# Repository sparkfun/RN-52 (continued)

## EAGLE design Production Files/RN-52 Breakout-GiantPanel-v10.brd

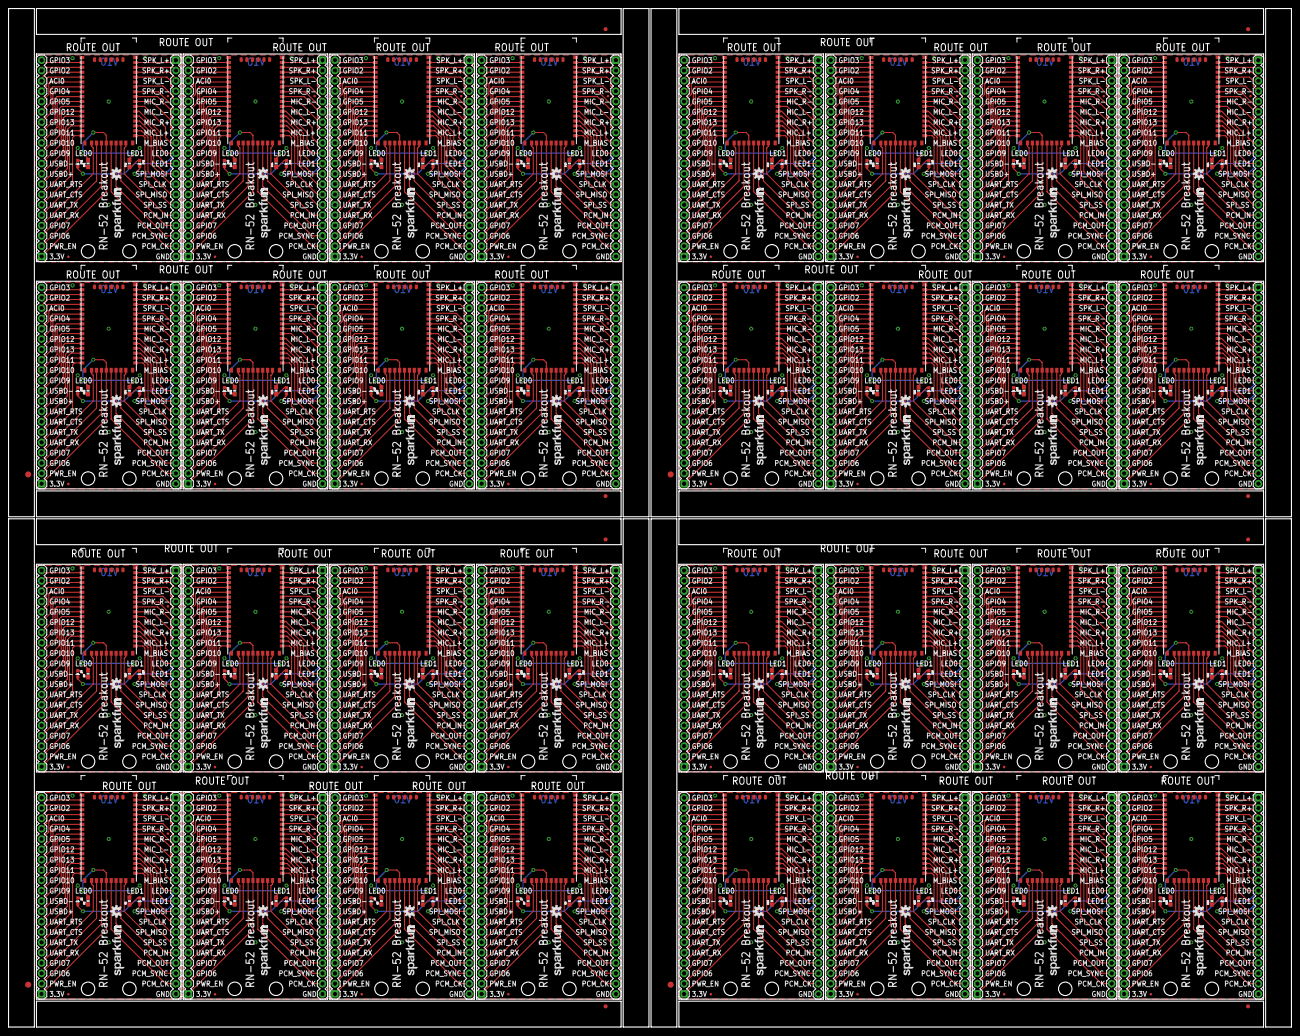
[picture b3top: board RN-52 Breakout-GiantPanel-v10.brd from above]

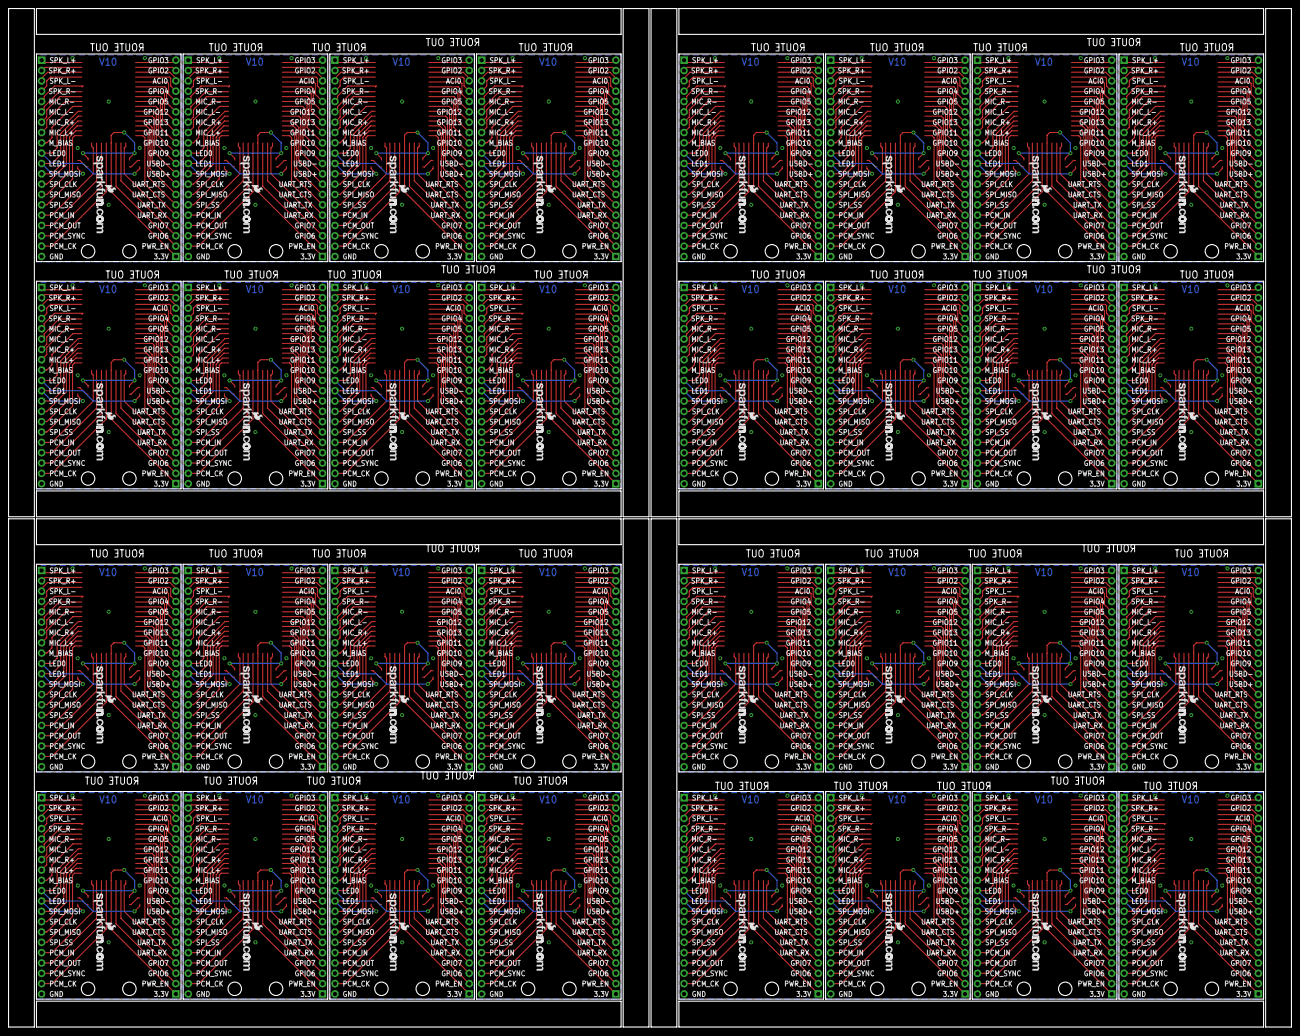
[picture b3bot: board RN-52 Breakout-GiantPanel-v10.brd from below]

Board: 2 copper layers, 315.5 x 250.4 mm, 460 parts (32 on the bottom side), 1344 nets.

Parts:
D1, D3, D5, D7, D9, D11, D13, D15, D17, D19, D21, D23, D25, D27, D29, D31, D33, D35, D37, D39, D41, D43, D45, D47, D49, D51, D53, D55, D57, D59, D61, D63: GREEN; LED-0603
D2, D4, D6, D8, D10, D12, D14, D16, D18, D20, D22, D24, D26, D28, D30, D32, D34, D36, D38, D40, D42, D44, D46, D48, D50, D52, D54, D56, D58, D60, D62, D64: RED; LED-0603
E$1, E$2, E$3, E$4, E$5, E$6, E$7, E$8, E$9, E$10, E$11, E$12, E$13, E$14, E$15, E$16, E$18, E$20, E$21, E$22, E$23, E$25, E$26, E$27, E$28, E$29, E$30, E$31, E$32, E$33, E$34, E$35, E$39, E$40, E$41, E$42, E$43, E$44, E$45, E$46, E$47, E$48, E$49, E$50, E$51, E$52, E$53, E$54, E$58, E$59, E$60, E$61, E$62, E$63, E$64, E$65, E$66, E$67, E$68, E$69, E$70, E$71, E$72, E$73: MICRO-FIDUCIAL
E$17, E$38, E$57, E$76: FIDUCIAL-1.5X3
E$19, E$24, E$36, E$37, E$55, E$56, E$74, E$75: FIDUCIAL-1X2
JP1, JP2, JP3, JP4, JP5, JP6, JP7, JP8, JP9, JP10, JP11, JP12, JP13, JP14, JP15, JP16, JP17, JP18, JP19, JP20, JP21, JP22, JP23, JP24, JP25, JP26, JP27, JP28, JP29, JP30, JP31, JP32, JP33, JP34, JP35, JP36, JP37, JP38, JP39, JP40, JP41, JP42, JP43, JP44, JP45, JP46, JP47, JP48, JP49, JP50, JP51, JP52, JP53, JP54, JP55, JP56, JP57, JP58, JP59, JP60, JP61, JP62, JP63, JP64: M20; 1X20
LOGO1, LOGO2, LOGO7, LOGO10, LOGO13, LOGO16, LOGO19, LOGO22, LOGO25, LOGO28, LOGO31, LOGO34, LOGO37, LOGO40, LOGO43, LOGO46, LOGO49, LOGO52, LOGO55, LOGO58, LOGO61, LOGO64, LOGO67, LOGO70, LOGO73, LOGO76, LOGO79, LOGO82, LOGO85, LOGO88, LOGO91, LOGO94: OSHW-LOGOS; OSHW-LOGO-S
LOGO3, LOGO5, LOGO8, LOGO11, LOGO14, LOGO17, LOGO20, LOGO23, LOGO26, LOGO29, LOGO32, LOGO35, LOGO38, LOGO41, LOGO44, LOGO47, LOGO50, LOGO53, LOGO56, LOGO59, LOGO62, LOGO65, LOGO68, LOGO71, LOGO74, LOGO77, LOGO80, LOGO83, LOGO86, LOGO89, LOGO92, LOGO95: LOGO-SFENEW; SFE-NEW-WEBLOGO
LOGO4, LOGO6, LOGO9, LOGO12, LOGO15, LOGO18, LOGO21, LOGO24, LOGO27, LOGO30, LOGO33, LOGO36, LOGO39, LOGO42, LOGO45, LOGO48, LOGO51, LOGO54, LOGO57, LOGO60, LOGO63, LOGO66, LOGO69, LOGO72, LOGO75, LOGO78, LOGO81, LOGO84, LOGO87, LOGO90, LOGO93, LOGO96: LOGO-SFENW2; SFE-NEW-WEB
R1, R2, R3, R4, R5, R6, R7, R8, R9, R10, R11, R12, R13, R14, R15, R16, R17, R18, R19, R20, R21, R22, R23, R24, R25, R26, R27, R28, R29, R30, R31, R32, R33, R34, R35, R36, R37, R38, R39, R40, R41, R42, R43, R44, R45, R46, R47, R48, R49, R50, R51, R52, R53, R54, R55, R56, R57, R58, R59, R60, R61, R62, R63, R64: 330; 0603-RES
STANDOFF1, STANDOFF2, STANDOFF3, STANDOFF4, STANDOFF5, STANDOFF6, STANDOFF7, STANDOFF8, STANDOFF9, STANDOFF10, STANDOFF11, STANDOFF12, STANDOFF13, STANDOFF14, STANDOFF15, STANDOFF16, STANDOFF17, STANDOFF18, STANDOFF19, STANDOFF20, STANDOFF21, STANDOFF22, STANDOFF23, STANDOFF24, STANDOFF25, STANDOFF26, STANDOFF27, STANDOFF28, STANDOFF29, STANDOFF30, STANDOFF31, STANDOFF32, STANDOFF33, STANDOFF34, STANDOFF35, STANDOFF36, STANDOFF37, STANDOFF38, STANDOFF39, STANDOFF40, STANDOFF41, STANDOFF42, STANDOFF43, STANDOFF44, STANDOFF45, STANDOFF46, STANDOFF47, STANDOFF48, STANDOFF49, STANDOFF50, STANDOFF51, STANDOFF52, STANDOFF53, STANDOFF54, STANDOFF55, STANDOFF56, STANDOFF57, STANDOFF58, STANDOFF59, STANDOFF60, STANDOFF61, STANDOFF62, STANDOFF63, STANDOFF64: STAND-OFF
U1, U2, U3, U4, U5, U6, U7, U8, U9, U10, U11, U12, U13, U14, U15, U16, U17, U18, U19, U20, U21, U22, U23, U24, U25, U26, U27, U28, U29, U30, U31, U32: BLUETOOTH-RN-52; RN-52

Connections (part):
3.3V: JP1.1, R1.2, R2.2, U1.20
3.3V1: JP3.1, R3.2, R4.2, U2.20
3.3V2: JP5.1, R5.2, R6.2, U3.20
3.3V3: JP7.1, R7.2, R8.2, U4.20
3.3V4: JP9.1, R9.2, R10.2, U5.20
3.3V5: JP11.1, R11.2, R12.2, U6.20
3.3V6: JP13.1, R13.2, R14.2, U7.20
3.3V7: JP15.1, R15.2, R16.2, U8.20
3.3V8: JP17.1, R17.2, R18.2, U9.20
3.3V9: JP19.1, R19.2, R20.2, U10.20
3.3V10: JP21.1, R21.2, R22.2, U11.20
3.3V11: JP23.1, R23.2, R24.2, U12.20
3.3V12: JP25.1, R25.2, R26.2, U13.20
3.3V13: JP27.1, R27.2, R28.2, U14.20
3.3V14: JP29.1, R29.2, R30.2, U15.20
3.3V15: JP31.1, R31.2, R32.2, U16.20
3.3V16: JP33.1, R33.2, R34.2, U17.20
3.3V17: JP35.1, R35.2, R36.2, U18.20
3.3V18: JP37.1, R37.2, R38.2, U19.20
3.3V19: JP39.1, R39.2, R40.2, U20.20
3.3V20: JP41.1, R41.2, R42.2, U21.20
3.3V21: JP43.1, R43.2, R44.2, U22.20
3.3V22: JP45.1, R45.2, R46.2, U23.20
3.3V23: JP47.1, R47.2, R48.2, U24.20
3.3V24: JP49.1, R49.2, R50.2, U25.20
3.3V25: JP51.1, R51.2, R52.2, U26.20
3.3V26: JP53.1, R53.2, R54.2, U27.20
3.3V27: JP55.1, R55.2, R56.2, U28.20
3.3V28: JP57.1, R57.2, R58.2, U29.20
3.3V29: JP59.1, R59.2, R60.2, U30.20
3.3V30: JP61.1, R61.2, R62.2, U31.20
3.3V31: JP63.1, R63.2, R64.2, U32.20
AIC0: JP1.18, U1.3
AIC1: JP3.18, U2.3
AIC2: JP5.18, U3.3
AIC3: JP7.18, U4.3
AIC4: JP9.18, U5.3
AIC5: JP11.18, U6.3
AIC6: JP13.18, U7.3
AIC7: JP15.18, U8.3
AIC8: JP17.18, U9.3
AIC9: JP19.18, U10.3
AIC10: JP21.18, U11.3
AIC11: JP23.18, U12.3
AIC12: JP25.18, U13.3
AIC13: JP27.18, U14.3
AIC14: JP29.18, U15.3
AIC15: JP31.18, U16.3
AIC16: JP33.18, U17.3
AIC17: JP35.18, U18.3
AIC18: JP37.18, U19.3
AIC19: JP39.18, U20.3
AIC20: JP41.18, U21.3
AIC21: JP43.18, U22.3
AIC22: JP45.18, U23.3
AIC23: JP47.18, U24.3
AIC24: JP49.18, U25.3
AIC25: JP51.18, U26.3
AIC26: JP53.18, U27.3
AIC27: JP55.18, U28.3
AIC28: JP57.18, U29.3
AIC29: JP59.18, U30.3
AIC30: JP61.18, U31.3
AIC31: JP63.18, U32.3
GND: JP2.20, U1.36, U1.G1, U1.G2, U1.G3, U1.G4, U1.RFG1, U1.RFG2, U1.RFG3, U1.RFG4, U1.RFG5, U1.RFG6
GND1: JP4.20, U2.36, U2.G1, U2.G2, U2.G3, U2.G4, U2.RFG1, U2.RFG2, U2.RFG3, U2.RFG4, U2.RFG5, U2.RFG6
GND2: JP6.20, U3.36, U3.G1, U3.G2, U3.G3, U3.G4, U3.RFG1, U3.RFG2, U3.RFG3, U3.RFG4, U3.RFG5, U3.RFG6
GND3: JP8.20, U4.36, U4.G1, U4.G2, U4.G3, U4.G4, U4.RFG1, U4.RFG2, U4.RFG3, U4.RFG4, U4.RFG5, U4.RFG6
GND4: JP10.20, U5.36, U5.G1, U5.G2, U5.G3, U5.G4, U5.RFG1, U5.RFG2, U5.RFG3, U5.RFG4, U5.RFG5, U5.RFG6
GND5: JP12.20, U6.36, U6.G1, U6.G2, U6.G3, U6.G4, U6.RFG1, U6.RFG2, U6.RFG3, U6.RFG4, U6.RFG5, U6.RFG6
GND6: JP14.20, U7.36, U7.G1, U7.G2, U7.G3, U7.G4, U7.RFG1, U7.RFG2, U7.RFG3, U7.RFG4, U7.RFG5, U7.RFG6
GND7: JP16.20, U8.36, U8.G1, U8.G2, U8.G3, U8.G4, U8.RFG1, U8.RFG2, U8.RFG3, U8.RFG4, U8.RFG5, U8.RFG6
GND8: JP18.20, U9.36, U9.G1, U9.G2, U9.G3, U9.G4, U9.RFG1, U9.RFG2, U9.RFG3, U9.RFG4, U9.RFG5, U9.RFG6
GND9: JP20.20, U10.36, U10.G1, U10.G2, U10.G3, U10.G4, U10.RFG1, U10.RFG2, U10.RFG3, U10.RFG4, U10.RFG5, U10.RFG6
GND10: JP22.20, U11.36, U11.G1, U11.G2, U11.G3, U11.G4, U11.RFG1, U11.RFG2, U11.RFG3, U11.RFG4, U11.RFG5, U11.RFG6
GND11: JP24.20, U12.36, U12.G1, U12.G2, U12.G3, U12.G4, U12.RFG1, U12.RFG2, U12.RFG3, U12.RFG4, U12.RFG5, U12.RFG6
GND12: JP26.20, U13.36, U13.G1, U13.G2, U13.G3, U13.G4, U13.RFG1, U13.RFG2, U13.RFG3, U13.RFG4, U13.RFG5, U13.RFG6
GND13: JP28.20, U14.36, U14.G1, U14.G2, U14.G3, U14.G4, U14.RFG1, U14.RFG2, U14.RFG3, U14.RFG4, U14.RFG5, U14.RFG6
GND14: JP30.20, U15.36, U15.G1, U15.G2, U15.G3, U15.G4, U15.RFG1, U15.RFG2, U15.RFG3, U15.RFG4, U15.RFG5, U15.RFG6
GND15: JP32.20, U16.36, U16.G1, U16.G2, U16.G3, U16.G4, U16.RFG1, U16.RFG2, U16.RFG3, U16.RFG4, U16.RFG5, U16.RFG6
GND16: JP34.20, U17.36, U17.G1, U17.G2, U17.G3, U17.G4, U17.RFG1, U17.RFG2, U17.RFG3, U17.RFG4, U17.RFG5, U17.RFG6
GND17: JP36.20, U18.36, U18.G1, U18.G2, U18.G3, U18.G4, U18.RFG1, U18.RFG2, U18.RFG3, U18.RFG4, U18.RFG5, U18.RFG6
GND18: JP38.20, U19.36, U19.G1, U19.G2, U19.G3, U19.G4, U19.RFG1, U19.RFG2, U19.RFG3, U19.RFG4, U19.RFG5, U19.RFG6
GND19: JP40.20, U20.36, U20.G1, U20.G2, U20.G3, U20.G4, U20.RFG1, U20.RFG2, U20.RFG3, U20.RFG4, U20.RFG5, U20.RFG6
GND20: JP42.20, U21.36, U21.G1, U21.G2, U21.G3, U21.G4, U21.RFG1, U21.RFG2, U21.RFG3, U21.RFG4, U21.RFG5, U21.RFG6
GND21: JP44.20, U22.36, U22.G1, U22.G2, U22.G3, U22.G4, U22.RFG1, U22.RFG2, U22.RFG3, U22.RFG4, U22.RFG5, U22.RFG6
GND22: JP46.20, U23.36, U23.G1, U23.G2, U23.G3, U23.G4, U23.RFG1, U23.RFG2, U23.RFG3, U23.RFG4, U23.RFG5, U23.RFG6
GND23: JP48.20, U24.36, U24.G1, U24.G2, U24.G3, U24.G4, U24.RFG1, U24.RFG2, U24.RFG3, U24.RFG4, U24.RFG5, U24.RFG6
GND24: JP50.20, U25.36, U25.G1, U25.G2, U25.G3, U25.G4, U25.RFG1, U25.RFG2, U25.RFG3, U25.RFG4, U25.RFG5, U25.RFG6
GND25: JP52.20, U26.36, U26.G1, U26.G2, U26.G3, U26.G4, U26.RFG1, U26.RFG2, U26.RFG3, U26.RFG4, U26.RFG5, U26.RFG6
GND26: JP54.20, U27.36, U27.G1, U27.G2, U27.G3, U27.G4, U27.RFG1, U27.RFG2, U27.RFG3, U27.RFG4, U27.RFG5, U27.RFG6
GND27: JP56.20, U28.36, U28.G1, U28.G2, U28.G3, U28.G4, U28.RFG1, U28.RFG2, U28.RFG3, U28.RFG4, U28.RFG5, U28.RFG6
GND28: JP58.20, U29.36, U29.G1, U29.G2, U29.G3, U29.G4, U29.RFG1, U29.RFG2, U29.RFG3, U29.RFG4, U29.RFG5, U29.RFG6
GND29: JP60.20, U30.36, U30.G1, U30.G2, U30.G3, U30.G4, U30.RFG1, U30.RFG2, U30.RFG3, U30.RFG4, U30.RFG5, U30.RFG6
GND30: JP62.20, U31.36, U31.G1, U31.G2, U31.G3, U31.G4, U31.RFG1, U31.RFG2, U31.RFG3, U31.RFG4, U31.RFG5, U31.RFG6
GND31: JP64.20, U32.36, U32.G1, U32.G2, U32.G3, U32.G4, U32.RFG1, U32.RFG2, U32.RFG3, U32.RFG4, U32.RFG5, U32.RFG6
GPIO1: JP3.20, U2.1
GPIO2: JP1.19, U1.2
GPIO3: JP1.20, U1.1
GPIO4: JP1.17, U1.4
GPIO5: JP1.16, U1.5
GPIO6: JP1.3, U1.18
GPIO7: JP1.4, U1.17
GPIO8: JP3.19, U2.2
GPIO9: JP1.11, U1.10
GPIO10: JP1.12, U1.9
GPIO11: JP1.13, U1.8
GPIO12: JP1.15, U1.6
GPIO13: JP1.14, U1.7
GPIO14: JP3.17, U2.4
GPIO15: JP3.16, U2.5
GPIO16: JP3.15, U2.6
GPIO17: JP3.14, U2.7
GPIO18: JP3.13, U2.8
GPIO19: JP3.12, U2.9
GPIO20: JP3.11, U2.10
GPIO21: JP3.4, U2.17
GPIO22: JP3.3, U2.18
GPIO23: JP5.20, U3.1
GPIO24: JP5.19, U3.2
GPIO25: JP5.17, U3.4
GPIO26: JP5.16, U3.5
GPIO27: JP5.15, U3.6
GPIO28: JP5.14, U3.7
GPIO29: JP5.13, U3.8
GPIO30: JP5.12, U3.9
GPIO31: JP5.11, U3.10
GPIO32: JP5.4, U3.17
GPIO33: JP5.3, U3.18
GPIO34: JP7.20, U4.1
GPIO35: JP7.19, U4.2
GPIO36: JP7.17, U4.4
GPIO37: JP7.16, U4.5
GPIO38: JP7.15, U4.6
GPIO39: JP7.14, U4.7
GPIO40: JP7.13, U4.8
GPIO41: JP7.12, U4.9
GPIO42: JP7.11, U4.10
GPIO43: JP7.4, U4.17
GPIO44: JP7.3, U4.18
GPIO45: JP9.20, U5.1
GPIO46: JP9.19, U5.2
GPIO47: JP9.17, U5.4
GPIO48: JP9.16, U5.5
GPIO49: JP9.15, U5.6
GPIO50: JP9.14, U5.7
GPIO51: JP9.13, U5.8
GPIO52: JP9.12, U5.9
GPIO53: JP9.11, U5.10
GPIO54: JP9.4, U5.17
GPIO55: JP9.3, U5.18
GPIO56: JP11.20, U6.1
GPIO57: JP11.19, U6.2
GPIO58: JP11.17, U6.4
GPIO59: JP11.16, U6.5
GPIO60: JP11.15, U6.6
GPIO61: JP11.14, U6.7
GPIO62: JP11.13, U6.8
GPIO63: JP11.12, U6.9
GPIO64: JP11.11, U6.10
GPIO65: JP11.4, U6.17
GPIO66: JP11.3, U6.18
GPIO67: JP13.20, U7.1
GPIO68: JP13.19, U7.2
GPIO69: JP13.17, U7.4
GPIO70: JP13.16, U7.5
GPIO71: JP13.15, U7.6
GPIO72: JP13.14, U7.7
GPIO73: JP13.13, U7.8
GPIO74: JP13.12, U7.9
GPIO75: JP13.11, U7.10
GPIO76: JP13.4, U7.17
GPIO77: JP13.3, U7.18
GPIO78: JP15.20, U8.1
GPIO79: JP15.19, U8.2
GPIO80: JP15.17, U8.4
GPIO81: JP15.16, U8.5
GPIO82: JP15.15, U8.6
GPIO83: JP15.14, U8.7
GPIO84: JP15.13, U8.8
GPIO85: JP15.12, U8.9
GPIO86: JP15.11, U8.10
GPIO87: JP15.4, U8.17
GPIO88: JP15.3, U8.18
GPIO89: JP17.20, U9.1
GPIO90: JP17.19, U9.2
GPIO91: JP17.17, U9.4
GPIO92: JP17.16, U9.5
GPIO93: JP17.15, U9.6
GPIO94: JP17.14, U9.7
GPIO95: JP17.13, U9.8
GPIO96: JP17.12, U9.9
GPIO97: JP17.11, U9.10
GPIO98: JP17.4, U9.17
GPIO99: JP17.3, U9.18
GPIO100: JP19.20, U10.1
GPIO101: JP19.19, U10.2
GPIO102: JP19.17, U10.4
GPIO103: JP19.16, U10.5
GPIO104: JP19.15, U10.6
GPIO105: JP19.14, U10.7
GPIO106: JP19.13, U10.8
GPIO107: JP19.12, U10.9
GPIO108: JP19.11, U10.10
GPIO109: JP19.4, U10.17
GPIO110: JP19.3, U10.18
GPIO111: JP21.20, U11.1
GPIO112: JP21.19, U11.2
GPIO113: JP21.17, U11.4
GPIO114: JP21.16, U11.5
GPIO115: JP21.15, U11.6
GPIO116: JP21.14, U11.7
GPIO117: JP21.13, U11.8
GPIO118: JP21.12, U11.9
GPIO119: JP21.11, U11.10
GPIO120: JP21.4, U11.17
GPIO121: JP21.3, U11.18
GPIO122: JP23.20, U12.1
GPIO123: JP23.19, U12.2
GPIO124: JP23.17, U12.4
GPIO125: JP23.16, U12.5
GPIO126: JP23.15, U12.6
GPIO127: JP23.14, U12.7
GPIO128: JP23.13, U12.8
GPIO129: JP23.12, U12.9
GPIO130: JP23.11, U12.10
GPIO131: JP23.4, U12.17
GPIO132: JP23.3, U12.18
GPIO133: JP25.20, U13.1
GPIO134: JP25.19, U13.2
GPIO135: JP25.17, U13.4
GPIO136: JP25.16, U13.5
GPIO137: JP25.15, U13.6
GPIO138: JP25.14, U13.7
GPIO139: JP25.13, U13.8
GPIO140: JP25.12, U13.9
GPIO141: JP25.11, U13.10
GPIO142: JP25.4, U13.17
GPIO143: JP25.3, U13.18
GPIO144: JP27.20, U14.1
GPIO145: JP27.19, U14.2
GPIO146: JP27.17, U14.4
GPIO147: JP27.16, U14.5
GPIO148: JP27.15, U14.6
GPIO149: JP27.14, U14.7
GPIO150: JP27.13, U14.8
GPIO151: JP27.12, U14.9
GPIO152: JP27.11, U14.10
GPIO153: JP27.4, U14.17
GPIO154: JP27.3, U14.18
GPIO155: JP29.20, U15.1
GPIO156: JP29.19, U15.2
GPIO157: JP29.17, U15.4
GPIO158: JP29.16, U15.5
GPIO159: JP29.15, U15.6
GPIO160: JP29.14, U15.7
GPIO161: JP29.13, U15.8
GPIO162: JP29.12, U15.9
GPIO163: JP29.11, U15.10
GPIO164: JP29.4, U15.17
GPIO165: JP29.3, U15.18
GPIO166: JP31.20, U16.1
GPIO167: JP31.19, U16.2
GPIO168: JP31.17, U16.4
GPIO169: JP31.16, U16.5
GPIO170: JP31.15, U16.6
GPIO171: JP31.14, U16.7
GPIO172: JP31.13, U16.8
GPIO173: JP31.12, U16.9
GPIO174: JP31.11, U16.10
GPIO175: JP31.4, U16.17
GPIO176: JP31.3, U16.18
GPIO177: JP33.20, U17.1
GPIO178: JP33.19, U17.2
GPIO179: JP33.17, U17.4
GPIO180: JP33.16, U17.5
GPIO181: JP33.15, U17.6
GPIO182: JP33.14, U17.7
GPIO183: JP33.13, U17.8
GPIO184: JP33.12, U17.9
GPIO185: JP33.11, U17.10
GPIO186: JP33.4, U17.17
GPIO187: JP33.3, U17.18
GPIO188: JP35.20, U18.1
GPIO189: JP35.19, U18.2
GPIO190: JP35.17, U18.4
GPIO191: JP35.16, U18.5
GPIO192: JP35.15, U18.6
GPIO193: JP35.14, U18.7
GPIO194: JP35.13, U18.8
GPIO195: JP35.12, U18.9
GPIO196: JP35.11, U18.10
GPIO197: JP35.4, U18.17
GPIO198: JP35.3, U18.18
GPIO199: JP37.20, U19.1
GPIO200: JP37.19, U19.2
GPIO201: JP37.17, U19.4
GPIO202: JP37.16, U19.5
GPIO203: JP37.15, U19.6
GPIO204: JP37.14, U19.7
GPIO205: JP37.13, U19.8
GPIO206: JP37.12, U19.9
GPIO207: JP37.11, U19.10
GPIO208: JP37.4, U19.17
GPIO209: JP37.3, U19.18
GPIO210: JP39.20, U20.1
GPIO211: JP39.19, U20.2
GPIO212: JP39.17, U20.4
GPIO213: JP39.16, U20.5
GPIO214: JP39.15, U20.6
GPIO215: JP39.14, U20.7
GPIO216: JP39.13, U20.8
GPIO217: JP39.12, U20.9
GPIO218: JP39.11, U20.10
GPIO219: JP39.4, U20.17
GPIO220: JP39.3, U20.18
GPIO221: JP41.20, U21.1
GPIO222: JP41.19, U21.2
GPIO223: JP41.17, U21.4
GPIO224: JP41.16, U21.5
GPIO225: JP41.15, U21.6
GPIO226: JP41.14, U21.7
GPIO227: JP41.13, U21.8
GPIO228: JP41.12, U21.9
GPIO229: JP41.11, U21.10
GPIO230: JP41.4, U21.17
GPIO231: JP41.3, U21.18
GPIO232: JP43.20, U22.1
GPIO233: JP43.19, U22.2
GPIO234: JP43.17, U22.4
GPIO235: JP43.16, U22.5
GPIO236: JP43.15, U22.6
GPIO237: JP43.14, U22.7
GPIO238: JP43.13, U22.8
GPIO239: JP43.12, U22.9
GPIO240: JP43.11, U22.10
GPIO241: JP43.4, U22.17
GPIO242: JP43.3, U22.18
GPIO243: JP45.20, U23.1
GPIO244: JP45.19, U23.2
GPIO245: JP45.17, U23.4
GPIO246: JP45.16, U23.5
GPIO247: JP45.15, U23.6
GPIO248: JP45.14, U23.7
GPIO249: JP45.13, U23.8
GPIO250: JP45.12, U23.9
GPIO251: JP45.11, U23.10
GPIO252: JP45.4, U23.17
GPIO253: JP45.3, U23.18
GPIO254: JP47.20, U24.1
GPIO255: JP47.19, U24.2
GPIO256: JP47.17, U24.4
GPIO257: JP47.16, U24.5
GPIO258: JP47.15, U24.6
GPIO259: JP47.14, U24.7
GPIO260: JP47.13, U24.8
GPIO261: JP47.12, U24.9
GPIO262: JP47.11, U24.10
GPIO263: JP47.4, U24.17
GPIO264: JP47.3, U24.18
GPIO265: JP49.20, U25.1
GPIO266: JP49.19, U25.2
GPIO267: JP49.17, U25.4
GPIO268: JP49.16, U25.5
GPIO269: JP49.15, U25.6
GPIO270: JP49.14, U25.7
GPIO271: JP49.13, U25.8
GPIO272: JP49.12, U25.9
GPIO273: JP49.11, U25.10
GPIO274: JP49.4, U25.17
GPIO275: JP49.3, U25.18
GPIO276: JP51.20, U26.1
GPIO277: JP51.19, U26.2
GPIO278: JP51.17, U26.4
GPIO279: JP51.16, U26.5
GPIO280: JP51.15, U26.6
GPIO281: JP51.14, U26.7
GPIO282: JP51.13, U26.8
GPIO283: JP51.12, U26.9
GPIO284: JP51.11, U26.10
GPIO285: JP51.4, U26.17
GPIO286: JP51.3, U26.18
GPIO287: JP53.20, U27.1
GPIO288: JP53.19, U27.2
GPIO289: JP53.17, U27.4
GPIO290: JP53.16, U27.5
GPIO291: JP53.15, U27.6
GPIO292: JP53.14, U27.7
GPIO293: JP53.13, U27.8
GPIO294: JP53.12, U27.9
GPIO295: JP53.11, U27.10
GPIO296: JP53.4, U27.17
GPIO297: JP53.3, U27.18
GPIO298: JP55.20, U28.1
GPIO299: JP55.19, U28.2
GPIO300: JP55.17, U28.4
GPIO301: JP55.16, U28.5
GPIO302: JP55.15, U28.6
GPIO303: JP55.14, U28.7
GPIO304: JP55.13, U28.8
GPIO305: JP55.12, U28.9
GPIO306: JP55.11, U28.10
GPIO307: JP55.4, U28.17
GPIO308: JP55.3, U28.18
GPIO309: JP57.20, U29.1
GPIO310: JP57.19, U29.2
GPIO311: JP57.17, U29.4
GPIO312: JP57.16, U29.5
GPIO313: JP57.15, U29.6
GPIO314: JP57.14, U29.7
GPIO315: JP57.13, U29.8
GPIO316: JP57.12, U29.9
GPIO317: JP57.11, U29.10
GPIO318: JP57.4, U29.17
GPIO319: JP57.3, U29.18
GPIO320: JP59.20, U30.1
GPIO321: JP59.19, U30.2
GPIO322: JP59.17, U30.4
GPIO323: JP59.16, U30.5
GPIO324: JP59.15, U30.6
GPIO325: JP59.14, U30.7
GPIO326: JP59.13, U30.8
GPIO327: JP59.12, U30.9
GPIO328: JP59.11, U30.10
GPIO329: JP59.4, U30.17
GPIO330: JP59.3, U30.18
GPIO331: JP61.20, U31.1
GPIO332: JP61.19, U31.2
GPIO333: JP61.17, U31.4
GPIO334: JP61.16, U31.5
GPIO335: JP61.15, U31.6
GPIO336: JP61.14, U31.7
GPIO337: JP61.13, U31.8
GPIO338: JP61.12, U31.9
GPIO339: JP61.11, U31.10
GPIO340: JP61.4, U31.17
GPIO341: JP61.3, U31.18
GPIO342: JP63.20, U32.1
GPIO343: JP63.19, U32.2
GPIO344: JP63.17, U32.4
GPIO345: JP63.16, U32.5
GPIO346: JP63.15, U32.6
GPIO347: JP63.14, U32.7
GPIO348: JP63.13, U32.8
GPIO349: JP63.12, U32.9
GPIO350: JP63.11, U32.10
GPIO351: JP63.4, U32.17
GPIO352: JP63.3, U32.18
LED0: D1.C, JP2.10, U1.30
LED1: D2.C, JP2.11, U1.29
LED2: D3.C, JP4.10, U2.30
LED3: D4.C, JP4.11, U2.29
LED4: D5.C, JP6.10, U3.30
LED5: D6.C, JP6.11, U3.29
LED6: D7.C, JP8.10, U4.30
LED7: D8.C, JP8.11, U4.29
LED8: D9.C, JP10.10, U5.30
LED9: D10.C, JP10.11, U5.29
LED10: D11.C, JP12.10, U6.30
LED11: D12.C, JP12.11, U6.29
LED12: D13.C, JP14.10, U7.30
LED13: D14.C, JP14.11, U7.29
LED14: D15.C, JP16.10, U8.30
LED15: D16.C, JP16.11, U8.29
LED16: D17.C, JP18.10, U9.30
LED17: D18.C, JP18.11, U9.29
LED18: D19.C, JP20.10, U10.30
LED19: D20.C, JP20.11, U10.29
LED20: D21.C, JP22.10, U11.30
LED21: D22.C, JP22.11, U11.29
LED22: D23.C, JP24.10, U12.30
LED23: D24.C, JP24.11, U12.29
LED24: D25.C, JP26.10, U13.30
LED25: D26.C, JP26.11, U13.29
LED26: D27.C, JP28.10, U14.30
LED27: D28.C, JP28.11, U14.29
LED28: D29.C, JP30.10, U15.30
LED29: D30.C, JP30.11, U15.29
LED30: D31.C, JP32.10, U16.30
LED31: D32.C, JP32.11, U16.29
LED32: D33.C, JP34.10, U17.30
LED33: D34.C, JP34.11, U17.29
LED34: D35.C, JP36.10, U18.30
LED35: D36.C, JP36.11, U18.29
LED36: D37.C, JP38.10, U19.30
LED37: D38.C, JP38.11, U19.29
LED38: D39.C, JP40.10, U20.30
LED39: D40.C, JP40.11, U20.29
LED40: D41.C, JP42.10, U21.30
LED41: D42.C, JP42.11, U21.29
LED42: D43.C, JP44.10, U22.30
LED43: D44.C, JP44.11, U22.29
LED44: D45.C, JP46.10, U23.30
LED45: D46.C, JP46.11, U23.29
LED46: D47.C, JP48.10, U24.30
LED47: D48.C, JP48.11, U24.29
LED48: D49.C, JP50.10, U25.30
LED49: D50.C, JP50.11, U25.29
LED50: D51.C, JP52.10, U26.30
LED51: D52.C, JP52.11, U26.29
LED52: D53.C, JP54.10, U27.30
LED53: D54.C, JP54.11, U27.29
LED54: D55.C, JP56.10, U28.30
LED55: D56.C, JP56.11, U28.29
LED56: D57.C, JP58.10, U29.30
LED57: D58.C, JP58.11, U29.29
LED58: D59.C, JP60.10, U30.30
LED59: D60.C, JP60.11, U30.29
LED60: D61.C, JP62.10, U31.30
LED61: D62.C, JP62.11, U31.29
LED62: D63.C, JP64.10, U32.30
LED63: D64.C, JP64.11, U32.29
MIC_BIAS: JP2.9, U1.31
MIC_BIAS1: JP4.9, U2.31
MIC_BIAS2: JP6.9, U3.31
MIC_BIAS3: JP8.9, U4.31
MIC_BIAS4: JP10.9, U5.31
MIC_BIAS5: JP12.9, U6.31
MIC_BIAS6: JP14.9, U7.31
MIC_BIAS7: JP16.9, U8.31
MIC_BIAS8: JP18.9, U9.31
MIC_BIAS9: JP20.9, U10.31
MIC_BIAS10: JP22.9, U11.31
MIC_BIAS11: JP24.9, U12.31
MIC_BIAS12: JP26.9, U13.31
MIC_BIAS13: JP28.9, U14.31
MIC_BIAS14: JP30.9, U15.31
MIC_BIAS15: JP32.9, U16.31
MIC_BIAS16: JP34.9, U17.31
MIC_BIAS17: JP36.9, U18.31
MIC_BIAS18: JP38.9, U19.31
MIC_BIAS19: JP40.9, U20.31
MIC_BIAS20: JP42.9, U21.31
MIC_BIAS21: JP44.9, U22.31
MIC_BIAS22: JP46.9, U23.31
MIC_BIAS23: JP48.9, U24.31
MIC_BIAS24: JP50.9, U25.31
MIC_BIAS25: JP52.9, U26.31
MIC_BIAS26: JP54.9, U27.31
MIC_BIAS27: JP56.9, U28.31
MIC_BIAS28: JP58.9, U29.31
MIC_BIAS29: JP60.9, U30.31
MIC_BIAS30: JP62.9, U31.31
MIC_BIAS31: JP64.9, U32.31
MIC_L+: JP2.8, U1.32
MIC_L+1: JP4.8, U2.32
MIC_L+2: JP6.8, U3.32
MIC_L+3: JP8.8, U4.32
MIC_L+4: JP10.8, U5.32
MIC_L+5: JP12.8, U6.32
MIC_L+6: JP14.8, U7.32
MIC_L+7: JP16.8, U8.32
MIC_L+8: JP18.8, U9.32
MIC_L+9: JP20.8, U10.32
MIC_L+10: JP22.8, U11.32
MIC_L+11: JP24.8, U12.32
MIC_L+12: JP26.8, U13.32
MIC_L+13: JP28.8, U14.32
MIC_L+14: JP30.8, U15.32
MIC_L+15: JP32.8, U16.32
MIC_L+16: JP34.8, U17.32
MIC_L+17: JP36.8, U18.32
MIC_L+18: JP38.8, U19.32
MIC_L+19: JP40.8, U20.32
MIC_L+20: JP42.8, U21.32
MIC_L+21: JP44.8, U22.32
MIC_L+22: JP46.8, U23.32
MIC_L+23: JP48.8, U24.32
MIC_L+24: JP50.8, U25.32
MIC_L+25: JP52.8, U26.32
MIC_L+26: JP54.8, U27.32
MIC_L+27: JP56.8, U28.32
MIC_L+28: JP58.8, U29.32
MIC_L+29: JP60.8, U30.32
MIC_L+30: JP62.8, U31.32
MIC_L+31: JP64.8, U32.32
MIC_L-: JP2.6, U1.34
MIC_L-1: JP4.6, U2.34
MIC_L-2: JP6.6, U3.34
MIC_L-3: JP8.6, U4.34
MIC_L-4: JP10.6, U5.34
MIC_L-5: JP12.6, U6.34
MIC_L-6: JP14.6, U7.34
MIC_L-7: JP16.6, U8.34
MIC_L-8: JP18.6, U9.34
MIC_L-9: JP20.6, U10.34
MIC_L-10: JP22.6, U11.34
MIC_L-11: JP24.6, U12.34
MIC_L-12: JP26.6, U13.34
MIC_L-13: JP28.6, U14.34
MIC_L-14: JP30.6, U15.34
MIC_L-15: JP32.6, U16.34
MIC_L-16: JP34.6, U17.34
MIC_L-17: JP36.6, U18.34
MIC_L-18: JP38.6, U19.34
MIC_L-19: JP40.6, U20.34
MIC_L-20: JP42.6, U21.34
MIC_L-21: JP44.6, U22.34
MIC_L-22: JP46.6, U23.34
MIC_L-23: JP48.6, U24.34
MIC_L-24: JP50.6, U25.34
MIC_L-25: JP52.6, U26.34
MIC_L-26: JP54.6, U27.34
MIC_L-27: JP56.6, U28.34
MIC_L-28: JP58.6, U29.34
MIC_L-29: JP60.6, U30.34
MIC_L-30: JP62.6, U31.34
MIC_L-31: JP64.6, U32.34
MIC_R+: JP2.7, U1.33
MIC_R+1: JP4.7, U2.33
MIC_R+2: JP6.7, U3.33
MIC_R+3: JP8.7, U4.33
MIC_R+4: JP10.7, U5.33
MIC_R+5: JP12.7, U6.33
MIC_R+6: JP14.7, U7.33
MIC_R+7: JP16.7, U8.33
MIC_R+8: JP18.7, U9.33
MIC_R+9: JP20.7, U10.33
MIC_R+10: JP22.7, U11.33
MIC_R+11: JP24.7, U12.33
MIC_R+12: JP26.7, U13.33
MIC_R+13: JP28.7, U14.33
MIC_R+14: JP30.7, U15.33
MIC_R+15: JP32.7, U16.33
MIC_R+16: JP34.7, U17.33
MIC_R+17: JP36.7, U18.33
MIC_R+18: JP38.7, U19.33
MIC_R+19: JP40.7, U20.33
MIC_R+20: JP42.7, U21.33
MIC_R+21: JP44.7, U22.33
MIC_R+22: JP46.7, U23.33
MIC_R+23: JP48.7, U24.33
MIC_R+24: JP50.7, U25.33
MIC_R+25: JP52.7, U26.33
MIC_R+26: JP54.7, U27.33
MIC_R+27: JP56.7, U28.33
MIC_R+28: JP58.7, U29.33
MIC_R+29: JP60.7, U30.33
MIC_R+30: JP62.7, U31.33
MIC_R+31: JP64.7, U32.33
MIC_R-: JP2.5, U1.35
MIC_R-1: JP4.5, U2.35
MIC_R-2: JP6.5, U3.35
MIC_R-3: JP8.5, U4.35
MIC_R-4: JP10.5, U5.35
MIC_R-5: JP12.5, U6.35
MIC_R-6: JP14.5, U7.35
MIC_R-7: JP16.5, U8.35
MIC_R-8: JP18.5, U9.35
MIC_R-9: JP20.5, U10.35
MIC_R-10: JP22.5, U11.35
MIC_R-11: JP24.5, U12.35
MIC_R-12: JP26.5, U13.35
MIC_R-13: JP28.5, U14.35
MIC_R-14: JP30.5, U15.35
MIC_R-15: JP32.5, U16.35
MIC_R-16: JP34.5, U17.35
MIC_R-17: JP36.5, U18.35
MIC_R-18: JP38.5, U19.35
MIC_R-19: JP40.5, U20.35
MIC_R-20: JP42.5, U21.35
MIC_R-21: JP44.5, U22.35
MIC_R-22: JP46.5, U23.35
MIC_R-23: JP48.5, U24.35
MIC_R-24: JP50.5, U25.35
MIC_R-25: JP52.5, U26.35
MIC_R-26: JP54.5, U27.35
MIC_R-27: JP56.5, U28.35
MIC_R-28: JP58.5, U29.35
MIC_R-29: JP60.5, U30.35
MIC_R-30: JP62.5, U31.35
MIC_R-31: JP64.5, U32.35
unnamed: D2.A, R2.1
unnamed: D1.A, R1.1
unnamed: D4.A, R4.1
unnamed: D3.A, R3.1
unnamed: D6.A, R6.1
unnamed: D5.A, R5.1
unnamed: D8.A, R8.1
unnamed: D7.A, R7.1
unnamed: D10.A, R10.1
unnamed: D9.A, R9.1
unnamed: D12.A, R12.1
unnamed: D11.A, R11.1
unnamed: D14.A, R14.1
unnamed: D13.A, R13.1
unnamed: D16.A, R16.1
unnamed: D15.A, R15.1
unnamed: D18.A, R18.1
unnamed: D17.A, R17.1
unnamed: D20.A, R20.1
unnamed: D19.A, R19.1
unnamed: D22.A, R22.1
unnamed: D21.A, R21.1
unnamed: D24.A, R24.1
unnamed: D23.A, R23.1
unnamed: D26.A, R26.1
unnamed: D25.A, R25.1
unnamed: D28.A, R28.1
unnamed: D27.A, R27.1
unnamed: D30.A, R30.1
unnamed: D29.A, R29.1
unnamed: D32.A, R32.1
unnamed: D31.A, R31.1
unnamed: D34.A, R34.1
unnamed: D33.A, R33.1
unnamed: D36.A, R36.1
unnamed: D35.A, R35.1
unnamed: D38.A, R38.1
unnamed: D37.A, R37.1
unnamed: D40.A, R40.1
unnamed: D39.A, R39.1
unnamed: D42.A, R42.1
unnamed: D41.A, R41.1
unnamed: D44.A, R44.1
unnamed: D43.A, R43.1
unnamed: D46.A, R46.1
unnamed: D45.A, R45.1
unnamed: D48.A, R48.1
unnamed: D47.A, R47.1
unnamed: D50.A, R50.1
unnamed: D49.A, R49.1
unnamed: D52.A, R52.1
unnamed: D51.A, R51.1
unnamed: D54.A, R54.1
unnamed: D53.A, R53.1
unnamed: D56.A, R56.1
unnamed: D55.A, R55.1
unnamed: D58.A, R58.1
unnamed: D57.A, R57.1
unnamed: D60.A, R60.1
unnamed: D59.A, R59.1
unnamed: D62.A, R62.1
unnamed: D61.A, R61.1
unnamed: D64.A, R64.1
unnamed: D63.A, R63.1
PCM_CLK: JP2.16, U1.24
PCM_CLK1: JP4.16, U2.24
PCM_CLK2: JP6.16, U3.24
PCM_CLK3: JP8.16, U4.24
PCM_CLK4: JP10.16, U5.24
PCM_CLK5: JP12.16, U6.24
PCM_CLK6: JP14.16, U7.24
PCM_CLK7: JP16.16, U8.24
PCM_CLK8: JP18.16, U9.24
PCM_CLK9: JP20.16, U10.24
PCM_CLK10: JP22.16, U11.24
PCM_CLK11: JP24.16, U12.24
PCM_CLK12: JP26.16, U13.24
PCM_CLK13: JP28.16, U14.24
PCM_CLK14: JP30.16, U15.24
PCM_CLK15: JP32.16, U16.24
PCM_CLK16: JP34.16, U17.24
PCM_CLK17: JP36.16, U18.24
PCM_CLK18: JP38.16, U19.24
PCM_CLK19: JP40.16, U20.24
PCM_CLK20: JP42.16, U21.24
PCM_CLK21: JP44.16, U22.24
PCM_CLK22: JP46.16, U23.24
PCM_CLK23: JP48.16, U24.24
PCM_CLK24: JP50.16, U25.24
PCM_CLK25: JP52.16, U26.24
PCM_CLK26: JP54.16, U27.24
PCM_CLK27: JP56.16, U28.24
PCM_CLK28: JP58.16, U29.24
PCM_CLK29: JP60.16, U30.24
PCM_CLK30: JP62.16, U31.24
PCM_CLK31: JP64.16, U32.24
PCM_IN: JP2.19, U1.21
PCM_IN1: JP4.19, U2.21
PCM_IN2: JP6.19, U3.21
PCM_IN3: JP8.19, U4.21
PCM_IN4: JP10.19, U5.21
PCM_IN5: JP12.19, U6.21
PCM_IN6: JP14.19, U7.21
PCM_IN7: JP16.19, U8.21
PCM_IN8: JP18.19, U9.21
PCM_IN9: JP20.19, U10.21
PCM_IN10: JP22.19, U11.21
PCM_IN11: JP24.19, U12.21
PCM_IN12: JP26.19, U13.21
PCM_IN13: JP28.19, U14.21
PCM_IN14: JP30.19, U15.21
PCM_IN15: JP32.19, U16.21
PCM_IN16: JP34.19, U17.21
PCM_IN17: JP36.19, U18.21
PCM_IN18: JP38.19, U19.21
PCM_IN19: JP40.19, U20.21
PCM_IN20: JP42.19, U21.21
PCM_IN21: JP44.19, U22.21
PCM_IN22: JP46.19, U23.21
PCM_IN23: JP48.19, U24.21
PCM_IN24: JP50.19, U25.21
PCM_IN25: JP52.19, U26.21
PCM_IN26: JP54.19, U27.21
PCM_IN27: JP56.19, U28.21
PCM_IN28: JP58.19, U29.21
PCM_IN29: JP60.19, U30.21
PCM_IN30: JP62.19, U31.21
PCM_IN31: JP64.19, U32.21
PCM_OUT: JP2.18, U1.22
PCM_OUT1: JP4.18, U2.22
PCM_OUT2: JP6.18, U3.22
PCM_OUT3: JP8.18, U4.22
PCM_OUT4: JP10.18, U5.22
PCM_OUT5: JP12.18, U6.22
PCM_OUT6: JP14.18, U7.22
PCM_OUT7: JP16.18, U8.22
PCM_OUT8: JP18.18, U9.22
PCM_OUT9: JP20.18, U10.22
PCM_OUT10: JP22.18, U11.22
PCM_OUT11: JP24.18, U12.22
PCM_OUT12: JP26.18, U13.22
PCM_OUT13: JP28.18, U14.22
PCM_OUT14: JP30.18, U15.22
PCM_OUT15: JP32.18, U16.22
PCM_OUT16: JP34.18, U17.22
PCM_OUT17: JP36.18, U18.22
PCM_OUT18: JP38.18, U19.22
PCM_OUT19: JP40.18, U20.22
PCM_OUT20: JP42.18, U21.22
PCM_OUT21: JP44.18, U22.22
PCM_OUT22: JP46.18, U23.22
PCM_OUT23: JP48.18, U24.22
PCM_OUT24: JP50.18, U25.22
PCM_OUT25: JP52.18, U26.22
PCM_OUT26: JP54.18, U27.22
PCM_OUT27: JP56.18, U28.22
PCM_OUT28: JP58.18, U29.22
PCM_OUT29: JP60.18, U30.22
PCM_OUT30: JP62.18, U31.22
PCM_OUT31: JP64.18, U32.22
PCM_SYNC: JP2.17, U1.23
PCM_SYNC1: JP4.17, U2.23
PCM_SYNC2: JP6.17, U3.23
PCM_SYNC3: JP8.17, U4.23
PCM_SYNC4: JP10.17, U5.23
PCM_SYNC5: JP12.17, U6.23
PCM_SYNC6: JP14.17, U7.23
PCM_SYNC7: JP16.17, U8.23
PCM_SYNC8: JP18.17, U9.23
PCM_SYNC9: JP20.17, U10.23
PCM_SYNC10: JP22.17, U11.23
PCM_SYNC11: JP24.17, U12.23
PCM_SYNC12: JP26.17, U13.23
PCM_SYNC13: JP28.17, U14.23
PCM_SYNC14: JP30.17, U15.23
PCM_SYNC15: JP32.17, U16.23
PCM_SYNC16: JP34.17, U17.23
PCM_SYNC17: JP36.17, U18.23
PCM_SYNC18: JP38.17, U19.23
PCM_SYNC19: JP40.17, U20.23
PCM_SYNC20: JP42.17, U21.23
PCM_SYNC21: JP44.17, U22.23
PCM_SYNC22: JP46.17, U23.23
PCM_SYNC23: JP48.17, U24.23
PCM_SYNC24: JP50.17, U25.23
PCM_SYNC25: JP52.17, U26.23
PCM_SYNC26: JP54.17, U27.23
PCM_SYNC27: JP56.17, U28.23
PCM_SYNC28: JP58.17, U29.23
PCM_SYNC29: JP60.17, U30.23
PCM_SYNC30: JP62.17, U31.23
PCM_SYNC31: JP64.17, U32.23
PWREN: JP1.2, U1.19
PWREN1: JP3.2, U2.19
PWREN2: JP5.2, U3.19
PWREN3: JP7.2, U4.19
PWREN4: JP9.2, U5.19
PWREN5: JP11.2, U6.19
PWREN6: JP13.2, U7.19
PWREN7: JP15.2, U8.19
PWREN8: JP17.2, U9.19
PWREN9: JP19.2, U10.19
PWREN10: JP21.2, U11.19
PWREN11: JP23.2, U12.19
PWREN12: JP25.2, U13.19
PWREN13: JP27.2, U14.19
PWREN14: JP29.2, U15.19
PWREN15: JP31.2, U16.19
PWREN16: JP33.2, U17.19
PWREN17: JP35.2, U18.19
PWREN18: JP37.2, U19.19
PWREN19: JP39.2, U20.19
PWREN20: JP41.2, U21.19
PWREN21: JP43.2, U22.19
PWREN22: JP45.2, U23.19
PWREN23: JP47.2, U24.19
PWREN24: JP49.2, U25.19
PWREN25: JP51.2, U26.19
PWREN26: JP53.2, U27.19
PWREN27: JP55.2, U28.19
PWREN28: JP57.2, U29.19
PWREN29: JP59.2, U30.19
PWREN30: JP61.2, U31.19
PWREN31: JP63.2, U32.19
SPI_CLK: JP2.13, U1.27
SPI_CLK1: JP4.13, U2.27
SPI_CLK2: JP6.13, U3.27
SPI_CLK3: JP8.13, U4.27
SPI_CLK4: JP10.13, U5.27
SPI_CLK5: JP12.13, U6.27
SPI_CLK6: JP14.13, U7.27
SPI_CLK7: JP16.13, U8.27
SPI_CLK8: JP18.13, U9.27
SPI_CLK9: JP20.13, U10.27
SPI_CLK10: JP22.13, U11.27
SPI_CLK11: JP24.13, U12.27
SPI_CLK12: JP26.13, U13.27
SPI_CLK13: JP28.13, U14.27
SPI_CLK14: JP30.13, U15.27
SPI_CLK15: JP32.13, U16.27
SPI_CLK16: JP34.13, U17.27
SPI_CLK17: JP36.13, U18.27
SPI_CLK18: JP38.13, U19.27
SPI_CLK19: JP40.13, U20.27
SPI_CLK20: JP42.13, U21.27
SPI_CLK21: JP44.13, U22.27
SPI_CLK22: JP46.13, U23.27
SPI_CLK23: JP48.13, U24.27
SPI_CLK24: JP50.13, U25.27
SPI_CLK25: JP52.13, U26.27
SPI_CLK26: JP54.13, U27.27
SPI_CLK27: JP56.13, U28.27
SPI_CLK28: JP58.13, U29.27
SPI_CLK29: JP60.13, U30.27
SPI_CLK30: JP62.13, U31.27
SPI_CLK31: JP64.13, U32.27
SPI_MISO: JP2.14, U1.26
SPI_MISO1: JP4.14, U2.26
SPI_MISO2: JP6.14, U3.26
SPI_MISO3: JP8.14, U4.26
SPI_MISO4: JP10.14, U5.26
SPI_MISO5: JP12.14, U6.26
SPI_MISO6: JP14.14, U7.26
SPI_MISO7: JP16.14, U8.26
SPI_MISO8: JP18.14, U9.26
SPI_MISO9: JP20.14, U10.26
SPI_MISO10: JP22.14, U11.26
SPI_MISO11: JP24.14, U12.26
SPI_MISO12: JP26.14, U13.26
SPI_MISO13: JP28.14, U14.26
SPI_MISO14: JP30.14, U15.26
SPI_MISO15: JP32.14, U16.26
SPI_MISO16: JP34.14, U17.26
SPI_MISO17: JP36.14, U18.26
SPI_MISO18: JP38.14, U19.26
SPI_MISO19: JP40.14, U20.26
SPI_MISO20: JP42.14, U21.26
SPI_MISO21: JP44.14, U22.26
SPI_MISO22: JP46.14, U23.26
SPI_MISO23: JP48.14, U24.26
SPI_MISO24: JP50.14, U25.26
SPI_MISO25: JP52.14, U26.26
SPI_MISO26: JP54.14, U27.26
SPI_MISO27: JP56.14, U28.26
SPI_MISO28: JP58.14, U29.26
SPI_MISO29: JP60.14, U30.26
SPI_MISO30: JP62.14, U31.26
SPI_MISO31: JP64.14, U32.26
SPI_MOSI: JP2.12, U1.28
SPI_MOSI1: JP4.12, U2.28
SPI_MOSI2: JP6.12, U3.28
SPI_MOSI3: JP8.12, U4.28
SPI_MOSI4: JP10.12, U5.28
SPI_MOSI5: JP12.12, U6.28
SPI_MOSI6: JP14.12, U7.28
SPI_MOSI7: JP16.12, U8.28
SPI_MOSI8: JP18.12, U9.28
SPI_MOSI9: JP20.12, U10.28
SPI_MOSI10: JP22.12, U11.28
SPI_MOSI11: JP24.12, U12.28
SPI_MOSI12: JP26.12, U13.28
SPI_MOSI13: JP28.12, U14.28
SPI_MOSI14: JP30.12, U15.28
SPI_MOSI15: JP32.12, U16.28
SPI_MOSI16: JP34.12, U17.28
SPI_MOSI17: JP36.12, U18.28
SPI_MOSI18: JP38.12, U19.28
SPI_MOSI19: JP40.12, U20.28
SPI_MOSI20: JP42.12, U21.28
SPI_MOSI21: JP44.12, U22.28
SPI_MOSI22: JP46.12, U23.28
SPI_MOSI23: JP48.12, U24.28
SPI_MOSI24: JP50.12, U25.28
SPI_MOSI25: JP52.12, U26.28
SPI_MOSI26: JP54.12, U27.28
SPI_MOSI27: JP56.12, U28.28
SPI_MOSI28: JP58.12, U29.28
SPI_MOSI29: JP60.12, U30.28
SPI_MOSI30: JP62.12, U31.28
SPI_MOSI31: JP64.12, U32.28
SPI_SS: JP2.15, U1.25
SPI_SS1: JP4.15, U2.25
SPI_SS2: JP6.15, U3.25
SPI_SS3: JP8.15, U4.25
SPI_SS4: JP10.15, U5.25
SPI_SS5: JP12.15, U6.25
SPI_SS6: JP14.15, U7.25
SPI_SS7: JP16.15, U8.25
SPI_SS8: JP18.15, U9.25
SPI_SS9: JP20.15, U10.25
SPI_SS10: JP22.15, U11.25
SPI_SS11: JP24.15, U12.25
SPI_SS12: JP26.15, U13.25
SPI_SS13: JP28.15, U14.25
SPI_SS14: JP30.15, U15.25
SPI_SS15: JP32.15, U16.25
SPI_SS16: JP34.15, U17.25
SPI_SS17: JP36.15, U18.25
SPI_SS18: JP38.15, U19.25
SPI_SS19: JP40.15, U20.25
SPI_SS20: JP42.15, U21.25
SPI_SS21: JP44.15, U22.25
SPI_SS22: JP46.15, U23.25
SPI_SS23: JP48.15, U24.25
SPI_SS24: JP50.15, U25.25
SPI_SS25: JP52.15, U26.25
SPI_SS26: JP54.15, U27.25
SPI_SS27: JP56.15, U28.25
SPI_SS28: JP58.15, U29.25
SPI_SS29: JP60.15, U30.25
SPI_SS30: JP62.15, U31.25
SPI_SS31: JP64.15, U32.25
SPKR_L+: JP2.1, U1.40
SPKR_L+1: JP4.1, U2.40
SPKR_L+2: JP6.1, U3.40
SPKR_L+3: JP8.1, U4.40
SPKR_L+4: JP10.1, U5.40
SPKR_L+5: JP12.1, U6.40
SPKR_L+6: JP14.1, U7.40
SPKR_L+7: JP16.1, U8.40
SPKR_L+8: JP18.1, U9.40
SPKR_L+9: JP20.1, U10.40
SPKR_L+10: JP22.1, U11.40
SPKR_L+11: JP24.1, U12.40
SPKR_L+12: JP26.1, U13.40
SPKR_L+13: JP28.1, U14.40
SPKR_L+14: JP30.1, U15.40
SPKR_L+15: JP32.1, U16.40
SPKR_L+16: JP34.1, U17.40
SPKR_L+17: JP36.1, U18.40
SPKR_L+18: JP38.1, U19.40
SPKR_L+19: JP40.1, U20.40
SPKR_L+20: JP42.1, U21.40
SPKR_L+21: JP44.1, U22.40
SPKR_L+22: JP46.1, U23.40
SPKR_L+23: JP48.1, U24.40
SPKR_L+24: JP50.1, U25.40
SPKR_L+25: JP52.1, U26.40
SPKR_L+26: JP54.1, U27.40
SPKR_L+27: JP56.1, U28.40
SPKR_L+28: JP58.1, U29.40
SPKR_L+29: JP60.1, U30.40
SPKR_L+30: JP62.1, U31.40
SPKR_L+31: JP64.1, U32.40
SPKR_L-: JP2.3, U1.38
SPKR_L-1: JP4.3, U2.38
SPKR_L-2: JP6.3, U3.38
SPKR_L-3: JP8.3, U4.38
SPKR_L-4: JP10.3, U5.38
SPKR_L-5: JP12.3, U6.38
SPKR_L-6: JP14.3, U7.38
SPKR_L-7: JP16.3, U8.38
SPKR_L-8: JP18.3, U9.38
SPKR_L-9: JP20.3, U10.38
SPKR_L-10: JP22.3, U11.38
SPKR_L-11: JP24.3, U12.38
SPKR_L-12: JP26.3, U13.38
SPKR_L-13: JP28.3, U14.38
SPKR_L-14: JP30.3, U15.38
SPKR_L-15: JP32.3, U16.38
SPKR_L-16: JP34.3, U17.38
SPKR_L-17: JP36.3, U18.38
SPKR_L-18: JP38.3, U19.38
SPKR_L-19: JP40.3, U20.38
SPKR_L-20: JP42.3, U21.38
SPKR_L-21: JP44.3, U22.38
SPKR_L-22: JP46.3, U23.38
SPKR_L-23: JP48.3, U24.38
SPKR_L-24: JP50.3, U25.38
SPKR_L-25: JP52.3, U26.38
SPKR_L-26: JP54.3, U27.38
SPKR_L-27: JP56.3, U28.38
SPKR_L-28: JP58.3, U29.38
SPKR_L-29: JP60.3, U30.38
SPKR_L-30: JP62.3, U31.38
SPKR_L-31: JP64.3, U32.38
SPKR_R+: JP2.2, U1.39
SPKR_R+1: JP4.2, U2.39
SPKR_R+2: JP6.2, U3.39
SPKR_R+3: JP8.2, U4.39
SPKR_R+4: JP10.2, U5.39
SPKR_R+5: JP12.2, U6.39
SPKR_R+6: JP14.2, U7.39
SPKR_R+7: JP16.2, U8.39
SPKR_R+8: JP18.2, U9.39
SPKR_R+9: JP20.2, U10.39
SPKR_R+10: JP22.2, U11.39
SPKR_R+11: JP24.2, U12.39
SPKR_R+12: JP26.2, U13.39
SPKR_R+13: JP28.2, U14.39
SPKR_R+14: JP30.2, U15.39
SPKR_R+15: JP32.2, U16.39
SPKR_R+16: JP34.2, U17.39
SPKR_R+17: JP36.2, U18.39
SPKR_R+18: JP38.2, U19.39
SPKR_R+19: JP40.2, U20.39
SPKR_R+20: JP42.2, U21.39
SPKR_R+21: JP44.2, U22.39
SPKR_R+22: JP46.2, U23.39
SPKR_R+23: JP48.2, U24.39
SPKR_R+24: JP50.2, U25.39
SPKR_R+25: JP52.2, U26.39
SPKR_R+26: JP54.2, U27.39
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
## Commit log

2013-03-11 Added .brd and .sch files
    Added .brd and .sch files
2013-06-20 Updated RN-52 to latest footprint
    Updated the RN-52 footprint to the latest specs from the newest
    datasheet.
    Changed some non-45 degree angles to 45 degrees.
    Minor silk changes.
2013-07-19 Added Version
    Added Version and cleaned up repo
2013-07-22 Edited .gitignore
    Edited .gitignore to ignore .DS_Store
2013-07-22 Added .gitignore
    Added .gitignore in upper level of folder
2013-07-22 deleted .DS_Store
2013-07-23 Created panels
    I've created the Giant Panel for Marvin Starscream, and that is able to
    break down into smaller panels for Optimus and Megatron.
2013-07-23 minor production file tweaks
    Added version number to production filenames. Added text to indicate
    mill areas on panels.
2014-03-07 Fixed PCM silkscreen error
    The PCM ports were mislabeled and were backwards from what they should
    have been. This has now bee corrected on the silk. The RN-52 part did
    not need editing.
2014-03-24 Revert 45a6439..b6272a8
    This rolls back to commit 45a6439f7a8237508462bf5798810a0a2ea111c3.
2014-03-24 Changed PCM silk
    PCM silk was backwards on previous versions. It is now flipped around
    and fixed.
2014-03-25 added local fiducials
2014-03-25 created v10 panel
2014-03-25 deleted panel
2014-03-25 Change Version number on copper
    Change Version number on copper from V10 to V_11.
2014-03-25 RE-created panel v11
2015-04-09 Updating README with new product links, modify directory names
